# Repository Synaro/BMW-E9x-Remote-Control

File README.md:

# BMW E9x Remote Control

Contrôleur embarqué expérimental pour orchestrer des fonctions distantes sur BMW
Série E9x à partir d'un cœur logiciel déterministe, testable et indépendant du
matériel.

> [!WARNING]
> Ce dépôt n'est pas un produit prêt à installer dans un véhicule. Le firmware
> fourni reste interdit de connexion au véhicule : l'acquisition TWAI passive
> est désactivée par défaut et réservée à un bus de banc qualifié. Aucun GPIO
> d'actionneur réel n'est configuré. Toute intégration physique exige une analyse de risques, des
> interverrouillages matériels, des essais sur banc et l'intervention d'une
> personne qualifiée. Le projet ne doit pas servir à contourner un antidémarrage,
> un système antivol ou une réglementation applicable.

## État du projet

### Implémenté et vérifié hors véhicule

- cœur déterministe : modèle d'état, politique de sécurité, machine d'état,
  décisions bornées et ports d'infrastructure ;
- configuration utilisateur versionnée, validée, protégée par CRC et persistée
  dans NVS sur ESP32-S3 ;
- configurateur et simulateur Windows, scénarios synthétiques, rejeu de traces
  et injections de défauts ;
- détection abstraite de trois impulsions de verrouillage avec gardes de
  provenance, fraîcheur et ordre, mais sans liaison BMW qualifiée ;
- couche CAN générique, file RX fixe et statistiques ; le pilote ESP-IDF/TWAI
  reste désactivé par défaut, démarre en `TWAI_MODE_LISTEN_ONLY` par défaut et
  peut sélectionner explicitement `TWAI_MODE_NORMAL` sur le profil Phase 3H,
  sans exposer encore aucune API d'émission ;
- contrats Capture V2, imports tabulaires et base de preuves Phase 3C/3D en
  lecture seule ;
- télémétrie V1 limitée aux trois fonctions réellement implémentées, toutes
  désactivées par défaut ;
- suites C++, Python, PlatformIO native/ESP32-S3 et simulateur Windows exécutées
  en intégration continue.

Ces validations sont logicielles et hors véhicule. Elles ne qualifient ni le
montage électrique K-CAN, ni une fonction de démarrage réel.

### Phase 3F/3G.1 — révisions K-CAN RX-only historiques

- design `KCAN_RX_ONLY_P3F` gelé, approvisionnement audité et PCB Phase 3G.1
  conservé comme révision historique reproductible ;
- carte d'achat actuelle : **ESP32-S3-DevKitC-1-N8R8** ; les 8 MiB de PSRAM
  supplémentaires ne sont pas utilisés par le firmware ;
- composants non commandés, montage non assemblé et non qualifié
  électriquement ;
- `R_LINK_TX` physiquement DNP : aucune pièce, aucun cavalier et aucune
  continuité TX autorisés ;
- aucune connexion à la BMW avant un PASS électrique complet et documenté ;
- aucune Phase 4 active. Cette révision ne doit plus être utilisée pour une
  nouvelle fabrication.

Les sources normatives sont volontairement séparées :

- [`BOM.csv`](hardware/kcan-rxonly/BOM.csv) décrit ce qui est utilisé ;
- [`procurement.csv`](hardware/kcan-rxonly/procurement.csv) décrit ce qui doit
  être acheté, avec les SKU, quantités économiques et snapshots datés ;
- [`netlist.csv`](hardware/kcan-rxonly/netlist.csv) décrit les connexions ;
- [`wiring.md`](hardware/kcan-rxonly/wiring.md) décrit l'assemblage et les
  contrôles. En cas de divergence, aucun résumé du README ne remplace ces
  fichiers.

### Phase 3H — matériel K-CAN entièrement bidirectionnel

La carte destinée à une future fabrication est désormais la Phase 3H :

- `ESP32-S3 GPIO5/TWAI_TX -> SN74LXC1T45-Q1 -> TJA1055 TXD` est un chemin
  cuivre continu ;
- `TJA1055 RXD -> ESP32-S3 GPIO4/TWAI_RX` reste le chemin de réception ;
- aucun jumper, pont de soudure, composant DNP ou gap cuivre ne verrouille TX ;
- le DevKit reste alimenté par USB et son 5 V n'est pas relié à `5V_TJA` ;
- le rail `5V_TJA` est fourni par le `TLS715B0EJV50XUMA1` validé en Phase 3G.1 ;
- les Gerbers, drills, BOM/CPL JLCPCB, BOM/centroid NextPCB, STEP, PDF, rendus
  et manifeste SHA-256 sont régénérés sous
  [`hardware/kcan-bidirectional-pcb/`](hardware/kcan-bidirectional-pcb/) ;
- aucune commande fabricant n'a été passée et aucune émission BMW n'est
  autorisée par cette révision.

La justification électrique, les GPIO, les marges logiques et les limites sont
documentés dans
[`docs/phase3h-bidirectional-kcan.md`](docs/phase3h-bidirectional-kcan.md).

### Non implémenté ou interdit à ce stade

L'adaptateur BMW réel de verrouillage, les actionneurs, les commandes
CAS/DDE/KL50 et le remote-start actif restent absents. Le **chemin électrique**
TX existe désormais sur la carte Phase 3H, mais aucune API ou commande
d'émission véhicule n'est implémentée.
Les observations communautaires ou diagnostiques ne deviennent jamais une
commande. Aucun essai BMW, rejeu ou contournement CAS/EWS/antidémarrage n'est
autorisé par l'état actuel du dépôt.

Le moteur de rejeu accepte des tableaux bornés et des fichiers de trace
canoniques. Aucun identifiant BMW n'est supposé : le profil de référence reste
au niveau `Discovery` et toutes ses sources de signaux restent `Candidate`.

## Architecture

```text
Commande / véhicule / timers
             |
             v
        Runtime embarqué  ------>  Ports d'infrastructure
             |                    (bus, E/S, notifications)
             v
        Controller
             |
             +------> SafetyPolicy
             |
             v
      Decision + actions bornées
```

Les dépendances vont vers les abstractions : la couche application connaît le
modèle du véhicule, mais ne connaît ni Arduino, ni ESP32, ni CAN, ni GPIO.

La machine d'état utilise les états suivants : `Idle`, `Authorizing`,
`Preparing`, `Cranking`, `Running`, `AwaitingTakeover`, `DriverControl`,
`Stopping` et `Fault`. Une donnée nécessaire absente ou périmée provoque un
refus ou un passage en défaut selon le contexte.

La description détaillée se trouve dans [docs/architecture.md](docs/architecture.md)
et les invariants dans [docs/safety.md](docs/safety.md). Le système de variantes
est décrit dans [docs/vehicle-profiles.md](docs/vehicle-profiles.md).
Le déclenchement par trois verrouillages et le cycle de reprise sont spécifiés
dans [docs/remote-session.md](docs/remote-session.md).
La frontière de confiance et les limites anti-rejeu des commandes sont décrites
dans [docs/lock-command-security.md](docs/lock-command-security.md).
Le contrat du futur décodeur CAN de verrouillage est défini dans
[docs/can-lock-command-adapter.md](docs/can-lock-command-adapter.md).
Les préférences, leurs limites et leur future persistance sont décrites dans
[docs/user-configuration.md](docs/user-configuration.md).
Le catalogue des fonctions actuellement implémentées est décrit dans
[docs/feature-framework.md](docs/feature-framework.md). Les idées non livrées
sont isolées dans [docs/backlog/features.md](docs/backlog/features.md).
Le premier moteur de télémétrie et ses alertes sont décrits dans
[docs/telemetry-alerts.md](docs/telemetry-alerts.md).
Le journal binaire redondant est spécifié dans
[docs/settings-persistence.md](docs/settings-persistence.md).
Le socle ESP-IDF, ses garde-fous et sa procédure de banc sont documentés dans
[docs/esp32s3-safe-foundation.md](docs/esp32s3-safe-foundation.md).
L'acquisition passive de Phase 3 et le format Capture V2 sont décrits dans
[docs/twai-listen-only-acquisition.md](docs/twai-listen-only-acquisition.md) et
[docs/capture-format-v2.md](docs/capture-format-v2.md).
Le choix du transceiver, le schéma de banc et la qualification électrique de
Phase 3B sont figés dans
[docs/phase3b-can-bench-hardware.md](docs/phase3b-can-bench-hardware.md).
Les contrats d'intégration des futurs relevés ISTA/TestO, la provenance et la
checklist de Phase 3C sont décrits dans
[docs/phase3c-vehicle-data-intake.md](docs/phase3c-vehicle-data-intake.md).
La qualification des premières preuves réelles et les inconnues restantes sont
décrites dans
[docs/phase3d-real-evidence-qualification.md](docs/phase3d-real-evidence-qualification.md).
La préparation K-CAN passive et le design RX-only gelé sont documentés dans
[docs/phase3e-kcan-passive-acquisition.md](docs/phase3e-kcan-passive-acquisition.md)
et
[docs/phase3f-kcan-rxonly-design-freeze.md](docs/phase3f-kcan-rxonly-design-freeze.md).
L'arrêt de conception PCB Phase 3G est motivé dans
[docs/phase3g-pcb-feasibility-audit.md](docs/phase3g-pcb-feasibility-audit.md).
La révision bidirectionnelle qui remplace ces cartes pour toute future
fabrication est décrite dans
[docs/phase3h-bidirectional-kcan.md](docs/phase3h-bidirectional-kcan.md).
Le configurateur PC est décrit dans
[docs/configurator.md](docs/configurator.md).
Le protocole entre configurateur et boîtier est spécifié dans
[docs/settings-protocol.md](docs/settings-protocol.md).
Le journal sémantique borné est décrit dans
[docs/diagnostic-journal.md](docs/diagnostic-journal.md).
La cible matérielle de banc, les achats autorisés et les limites avant connexion
au véhicule sont détaillés dans
[docs/hardware-v1-reference.md](docs/hardware-v1-reference.md).
La barrière logicielle placée devant le futur pilote de sorties est spécifiée
dans [docs/actuator-safety-supervisor.md](docs/actuator-safety-supervisor.md).
Le protocole local du bac à sable graphique est documenté dans
[docs/sandbox-protocol.md](docs/sandbox-protocol.md).

## Validation locale

Prérequis : un compilateur C++17. Sous Windows avec `g++.exe` disponible :

```powershell
./scripts/test.ps1
```

Les tests de l'importeur Python n'installent aucune dépendance externe :

```powershell
python -m unittest discover -s tools -p 'test_*.py' -v
```

Compilation du firmware natif avec PlatformIO :

```powershell
pio run -e native
```

La cible exacte du prototype ESP32-S3 peut être vérifiée avec :

```powershell
pio run -e esp32s3dev
```

Cette carte est la cible du prototype de banc, pas celle de l'installation
automobile définitive. Le firmware dessert le protocole local de configuration
sur USB. L'acquisition TWAI n'est activable que par une configuration locale
`BENCH_ONLY` et ne possède aucun chemin d'émission ; aucune sortie véhicule
n'est activée.

Avec CMake :

```sh
cmake -S . -B build
cmake --build build
ctest --test-dir build --output-on-failure
```

## Organisation

```text
include/bmw_remote/domain/          Modèle métier du véhicule
include/bmw_remote/application/     Sécurité, événements, décisions, contrôleur
include/bmw_remote/infrastructure/  Contrats des adaptateurs et runtime
include/bmw_remote/simulation/      Protocole synthétique hors véhicule
libs/can-core/                       Modèle et réception CAN génériques, sans BMW
src/                                Implémentations et firmware ESP32-S3
tests/                              Scénarios hôte
tools/                              Simulateur et importeur de traces PC
vehicle-data/                       Profils, observations, preuves et imports versionnés
scenarios/                          Traces synthétiques partageables
docs/                               Architecture, sécurité et intégration
```

## Configurateur utilisateur Windows

Le fichier personnel peut être créé ou modifié sans éditer de texte à la main :

```powershell
.\scripts\configure.ps1
```

L'assistant conserve une valeur lorsque l'utilisateur appuie simplement sur
Entrée, valide toutes les limites de sûreté puis écrit
`config/user-settings.conf`. Le contrôle du capot peut notamment être placé sur
`disabled` pour une E9x qui ne possède pas ce capteur.

La configuration produite peut être contrôlée puis exécutée immédiatement dans
le simulateur :

```powershell
.\scripts\configure.ps1 -Check
.\scripts\simulate.ps1 -ConfigPath .\config\user-settings.conf
```

L'exécutable généré se trouve dans `build/bmw_remote_configurator.exe`. Le codec
et le service communiquent avec le prototype par son port série USB. Pour lister
les ports puis lire ou écrire le boîtier :

```powershell
.\scripts\configure.ps1 -ListDevices
.\scripts\configure.ps1 -ProbeDevice COM3
.\scripts\configure.ps1 -ReadDevice COM3
.\scripts\configure.ps1 -WriteDevice COM3
```

Une écriture n'est déclarée réussie qu'après relecture et comparaison complète.
Voir [docs/configurator.md](docs/configurator.md).

Le premier essai avec une carte neuve est automatisé et utilise une
configuration de banc où le démarrage distant reste désactivé :

```powershell
.\scripts\first-usb-test.ps1 -Port COM3
```

## Simulateur applicatif

Sous Windows, le moyen le plus simple est l'interface graphique :

```powershell
.\scripts\simulator-gui.ps1
```

Le fichier `scripts/start-simulator-gui.cmd` peut aussi être ouvert par double
clic. L'interface compile le simulateur uniquement lorsque ses sources sont
plus récentes, permet de choisir un scénario, un fichier de configuration ou
une trace, puis affiche et copie le rapport. Le bouton **Ouvrir le bac à sable**
garde une session vivante : l'utilisateur peut modifier les portes, le capot,
le frein, le rapport et le régime moteur, déclencher les timers et observer en
direct l'état, les sorties simulées et les défauts. Les températures moteur et
boîte, la régénération FAP et leurs trois fonctions V1 peuvent également être
injectées ou désactivées séparément. Elle reste entièrement
locale et ne se connecte à aucun véhicule.

Sous Windows, l'exécutable interactif peut être construit avec :

```powershell
.\scripts\build-simulator.ps1
.\build\bmw_remote_simulator.exe
```

Le catalogue des fonctions actuellement implémentées est affichable
sans lancer de scénario :

```powershell
.\build\bmw_remote_simulator.exe --list-features
```

Quinze scénarios permettent de tester le parcours nominal, le capot obligatoire
ou facultatif, la reprise conducteur, la perte, le retard et la corruption des
données, un profil utilisateur, la récupération du stockage et la liaison de
configuration, la garde anti-rejeu et l'adaptateur CAN qualifié sur un vecteur
fictif, le watchdog et les retours d'actionneurs simulés, ainsi que leur
propagation complète dans le runtime. Un scénario précis
peut aussi être compilé et exécuté avec :

```powershell
.\scripts\simulate.ps1 -Scenario hood-optional
.\scripts\simulate.ps1 -Scenario takeover-timeout
.\scripts\simulate.ps1 -Scenario takeover-confirmed
.\scripts\simulate.ps1 -Scenario signal-loss
.\scripts\simulate.ps1 -Scenario signal-delay
.\scripts\simulate.ps1 -Scenario frame-corruption
.\scripts\simulate.ps1 -ConfigPath .\config\user-settings.example.conf
.\scripts\simulate.ps1 -Scenario settings-recovery
.\scripts\simulate.ps1 -Scenario settings-link
.\scripts\simulate.ps1 -Scenario lock-replay-guard
.\scripts\simulate.ps1 -Scenario qualified-lock-adapter
.\scripts\simulate.ps1 -Scenario actuator-supervisor
.\scripts\simulate.ps1 -Scenario supervised-runtime
```

Chaque parcours affiche aussi le journal chronologique des commandes,
transitions, refus et défauts. Le résultat attendu est affiché sous la forme
`scenario_result: PASS` et le code de sortie reste non nul si le comportement
diverge.

Voir [docs/simulator.md](docs/simulator.md) pour la CLI et
[docs/can-replay.md](docs/can-replay.md) pour le contrat du moteur de rejeu.

Le simulateur accepte aussi une trace canonique externe :

```powershell
./scripts/simulate.ps1 ./scenarios/synthetic_idle.cantrace.csv
```

Pour convertir une capture reconnue par `python-can`, voir
[docs/trace-import.md](docs/trace-import.md). Les captures privées restent hors
du dépôt via `captures/private/`.

Une comparaison synthétique capot fermé / ouvert peut être lancée avec :

```powershell
./scripts/analyze-trace-change.ps1 `
  ./scenarios/synthetic_idle.cantrace.csv `
  ./scenarios/synthetic_hood_open.cantrace.csv
```

Le protocole destiné aux premières observations réelles est décrit dans
[docs/read-only-discovery.md](docs/read-only-discovery.md).

Une session privée d'inventaire K+DCAN peut être préparée sans enregistrer le
VIN :

```powershell
.\scripts\new-diagnostic-session.ps1 -SessionName e90-reference-01
```

Voir [docs/diagnostic-inventory.md](docs/diagnostic-inventory.md) avant d'ouvrir
une fonction dans ISTA, INPA ou Tool32.

Pour VS Code, PlatformIO génère localement `.vscode/c_cpp_properties.json` avec
les paramètres de l'environnement actif ; ce fichier reste hors Git car il
contient des chemins propres à la machine. `compile_flags.txt` configure le mode
de repli de `clangd`. Si d'anciens diagnostics restent affichés après une mise à
jour, exécuter `PlatformIO: Rebuild IntelliSense Index`, puis
`C/C++: Reset IntelliSense Database` et recharger la fenêtre.

## Capture CAN passive

Un outil PC peut produire directement une trace canonique depuis une interface
`python-can` dont le mode silencieux a été intégré explicitement :

```powershell
.\scripts\capture-can-trace.ps1 `
  -Interface pcan `
  -Channel PCAN_USBBUS1 `
  -Bitrate 500000 `
  -Duration 10 `
  -OutputPath .\captures\private\session-01\baseline.cantrace.csv
```

Le débit ci-dessus est uniquement un exemple et doit être confirmé avant la
connexion. L'outil ne contient aucun appel d'émission et refuse les pilotes non
qualifiés. Le câble K+DCAN reste réservé au diagnostic : il n'est pas supposé
fournir une capture CAN brute. Voir
[docs/capture-qualification.md](docs/capture-qualification.md).

## Principes de contribution

Toute évolution doit conserver la séparation entre métier et matériel, échouer
de manière sûre, rester déterministe et ajouter des tests aux nouvelles
transitions. Voir [CONTRIBUTING.md](CONTRIBUTING.md).

## Origine et inspiration

Le concept général est inspiré du dépôt
[AlbertoMarziali/bmw_remote_start](https://github.com/AlbertoMarziali/bmw_remote_start).
Ce projet est une implémentation indépendante : aucun code du dépôt de référence
n'a été copié. L'objectif est une architecture plus modulaire, explicite et
adaptée à une validation progressive.

## Licence

Distribué sous licence MIT. Voir [LICENSE](LICENSE).

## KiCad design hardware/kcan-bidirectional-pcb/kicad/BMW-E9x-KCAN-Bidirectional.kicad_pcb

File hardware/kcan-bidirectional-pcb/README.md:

# Phase 3H — carte K-CAN bidirectionnelle

Ce dossier définit la révision matérielle destinée à remplacer la carte
RX-only Phase 3G/3G.1 pour une future fabrication. Les dossiers et tags des
anciennes phases restent historiques et ne sont pas modifiés.

La carte Phase 3H fournit les deux chemins électriques complets :

```text
GPIO5 / TWAI_TX -> R5 -> U2 A -> U2 B -> U1 TXD -> K-CAN
K-CAN -> U1 RXD -> R7 -> GPIO4 / TWAI_RX
```

U2 est un `SN74LXC1T45QDCKRQ1` alimenté en 3,3 V côté A et 5 V côté B.
Il remplace le buffer mono-alimentation Phase 3G. Il ne constitue pas un
verrou : `DIR` est fixé à A vers B et le chemin TX est toujours câblé.

Il n'existe aucun jumper TX, pont de soudure, composant DNP, `R_LINK_TX`, zone
keepout ou coupure cuivre permettant/désactivant la transmission. Le mode
listen-only reste disponible uniquement comme configuration logicielle TWAI.

## Contenu

- `kicad/` : schéma et PCB KiCad 10 Phase 3H ;
- `BOM_PHASE3H.csv` : BOM normative par carte ;
- `netlist_PHASE3H.csv` : connexions normatives et chemins fonctionnels ;
- `pin-review.csv` : revue des broches critiques ;
- `procurement_PHASE3H.csv` : références de sourcing, sans ordre d'achat ;
- `manufacturing/` : artefacts régénérés depuis cette révision uniquement.

La régénération s'effectue avec :

```powershell
python tools/generate_phase3h_kicad.py schematic
& 'C:\Users\synar\AppData\Local\Programs\KiCad\10.0\bin\python.exe' tools/generate_phase3h_kicad.py pcb
./tools/generate_phase3h_manufacturing.ps1
./tools/generate_phase3h_nextpcb.ps1
```

Ces commandes ne contactent aucun fabricant et ne passent aucune commande.

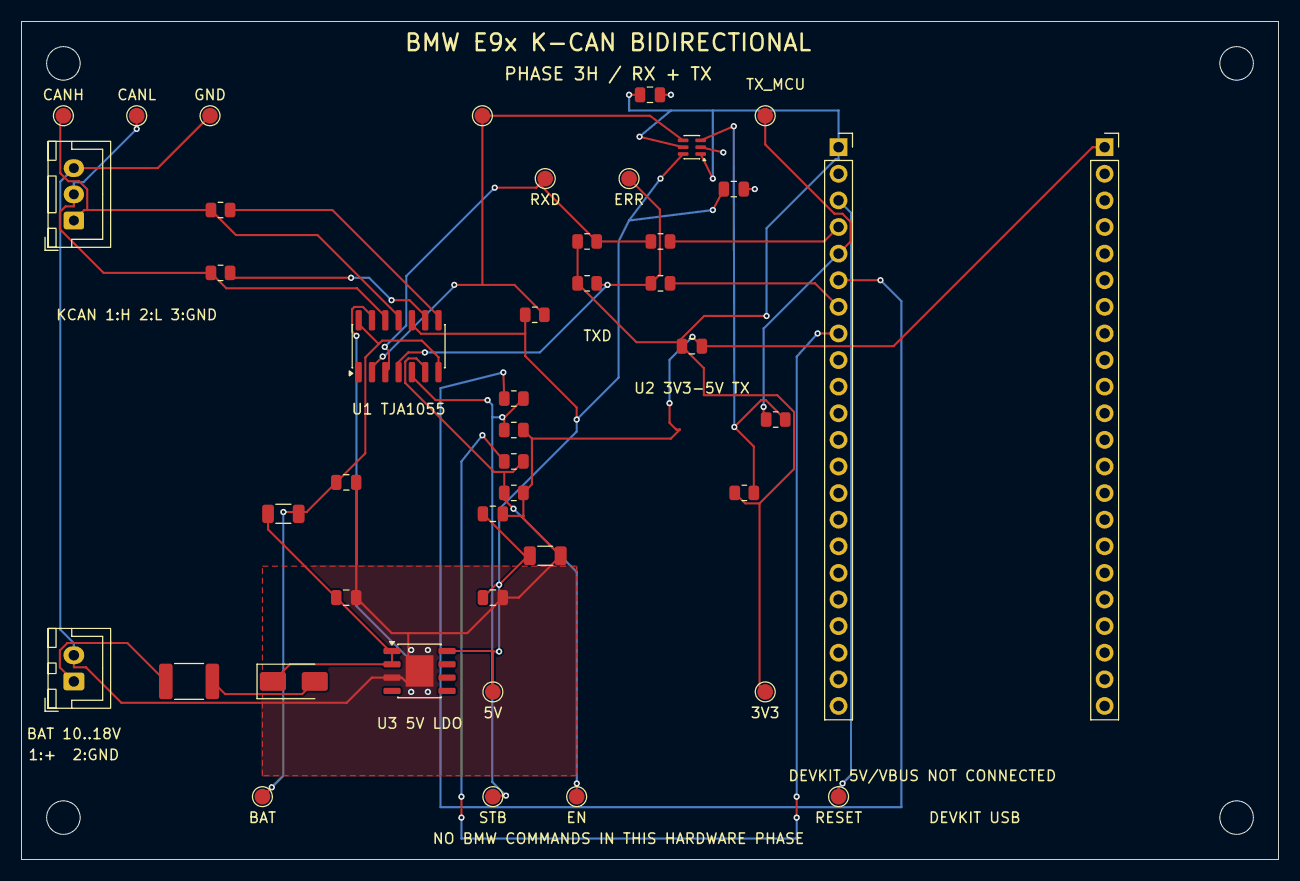
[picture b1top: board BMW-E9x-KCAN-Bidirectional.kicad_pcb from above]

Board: 2 copper layers, 120.0 x 80.0 mm, 48 parts (0 on the bottom side), 23 nets.

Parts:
C1: C_REG_IN 100n 50V; C_0805_2012Metric
C2: C_REG_OUT 2.2u 25V; C_0805_2012Metric
C3: C_VCC 100n; C_0805_2012Metric
C4: C_VCC 22u 10V; C_1206_3216Metric
C5: C_BAT 10n 50V; C_0805_2012Metric
C6: C_U2 100n; C_0805_2012Metric
C7: 100n / C_U2_5V; C_0805_2012Metric
C8: 100n / C_U2_3V3; C_0805_2012Metric
D1: D_BAT SS16; D_SMA
F1: F_BAT MINISMDC010F-2; Fuse_1812_4532Metric_Pad1.30x3.40mm_Reviewed
H1: ESP32-S3 DEVKIT J1; PinSocket_1x22_P2.54mm_Vertical
H2: ESP32-S3 DEVKIT J3; PinSocket_1x22_P2.54mm_Vertical
J1: J_BAT 10..18V BENCH; JST_XH_B2B-XH-A_1x02_P2.50mm_Vertical
J2: J_KCAN H L GND; JST_XH_B3B-XH-A_1x03_P2.50mm_Vertical
MH1, MH2, MH3, MH4: M3; MountingHole_3.2mm_M3
R1: R_BAT 1k; R_1206_3216Metric
R2: R_TXD 10k; R_0805_2012Metric
R4: R_A 100k; R_0805_2012Metric
R5: R_TX_SER 1k; R_0805_2012Metric
R6: R_RX_PULL 3.3k; R_0805_2012Metric
R7: R_RX_SER 1k; R_0805_2012Metric
R8: R_ERR_PULL 3.3k; R_0805_2012Metric
R9: R_ERR_SER 1k; R_0805_2012Metric
R10: R_STB_SER 1k; R_0805_2012Metric
R11: R_STB_PD 10k; R_0805_2012Metric
R12: R_EN_SER 1k; R_0805_2012Metric
R13: R_EN_PD 10k; R_0805_2012Metric
R14: R_RTH 5.62k; R_0805_2012Metric
R15: R_RTL 5.62k; R_0805_2012Metric
TP1: BAT; TestPoint_Pad_D1.5mm
TP2: 5V; TestPoint_Pad_D1.5mm
TP3: 3V3; TestPoint_Pad_D1.5mm
TP5: TXD; TestPoint_Pad_D1.5mm
TP7: TWAI_TX; TestPoint_Pad_D1.5mm
TP8: RESET; TestPoint_Pad_D1.5mm
TP9: STB; TestPoint_Pad_D1.5mm
TP10: EN; TestPoint_Pad_D1.5mm
TP11: RXD; TestPoint_Pad_D1.5mm
TP12: ERR; TestPoint_Pad_D1.5mm
TP13: CANH; TestPoint_Pad_D1.5mm
TP14: CANL; TestPoint_Pad_D1.5mm
TP15: GND; TestPoint_Pad_D1.5mm
U1: TJA1055T/3/2Z; SO-14_3.9x8.65mm_P1.27mm
U2: SN74LXC1T45QDCKRQ1; SOT-363_SC-70-6
U3: TLS715B0EJV50XUMA1; Infineon_PG-DSO-8-52_3.9x4.9mm_EP2.65x3mm_NoViaInPad

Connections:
3V3: C6.1, C8.1, H1.1, R4.1, R6.1, R8.1, TP3.1, U2.1, U2.5
5V_TJA: C2.1, C3.1, C4.1, C7.1, R2.1, TP2.1, U1.10, U2.6, U3.8
BAT_FUSED: D1.2, F1.2
BAT_INPUT: F1.1, J1.1
BAT_LOCAL: C5.1, R1.2, TP1.1, U1.7, U1.14
BAT_PROTECTED: C1.1, D1.1, R1.1, U3.1, U3.2
GND: C1.2, C2.2, C3.2, C4.2, C5.2, C6.2, C7.2, C8.2, H2.1, J1.2, J2.3, R11.2, R13.2, TP15.1, U1.13, U2.2, U3.3, U3.9
KCAN_EN: R12.2, R13.1, TP10.1, U1.6
KCAN_EN_MCU: H1.8, R12.1
KCAN_ERR_MCU: H1.7, R9.2
KCAN_ERR_OD: R8.2, R9.1, TP12.1, U1.4
KCAN_H: J2.1, R14.1, TP13.1, U1.11
KCAN_L: J2.2, R15.1, TP14.1, U1.12
KCAN_RXD_OD: R6.2, R7.1, TP11.1, U1.3
KCAN_RX_MCU: H1.4, R7.2
KCAN_STB: R10.2, R11.1, TP9.1, U1.5
KCAN_STB_MCU: H1.6, R10.1
KCAN_TXD: R2.2, TP5.1, U1.2, U2.4
KCAN_TX_A: R4.2, R5.2, U2.3
KCAN_TX_MCU: H1.5, R5.1, TP7.1
RESET: H1.3, TP8.1
RTH: R14.2, U1.8
RTL: R15.2, U1.9

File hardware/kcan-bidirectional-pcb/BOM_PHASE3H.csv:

reference,quantity,manufacturer,mpn,value,package,assembly,role
U1,1,NXP,TJA1055T/3/2Z,TJA1055T/3,SO-14_3.9x8.7mm,MOUNT,ISO11898-3 full bidirectional K-CAN transceiver
U2,1,Texas Instruments,SN74LXC1T45QDCKRQ1,SN74LXC1T45-Q1,SC70-6 DCK,MOUNT,Automotive dual-supply 3V3-to-5V TX translator
U3,1,Infineon,TLS715B0EJV50XUMA1,5V 150mA,PG-DSO-8-52 EP,MOUNT,Dedicated 5V_TJA regulator
DEV1,1,Espressif Systems,ESP32-S3-DEVKITC-1-N8R8,DevKitC-1,Removable module,USER_INSTALL,USB-powered TWAI controller
H1 H2,2,Samtec,SSQ-122-03-G-S,1x22 female,2.54mm THT,MOUNT,DevKit sockets
F1,1,Littelfuse,MINISMDC010F-2,0.10A hold,1812,MOUNT,F_BAT input current protection
D1,1,Vishay,SS16-E3/61T,SS16 / D_BAT,SMA,MOUNT,Input reverse-polarity protection
R1,1,Yageo,RC1206FR-071KL,1k 1%,1206,MOUNT,R_BAT TJA BAT series
R2 R11 R13,3,Yageo,RC0805FR-0710KL,10k 1%,0805,MOUNT,TXD recessive bias and STB EN reset pulldowns
R4,1,Yageo,RC0805FR-07100KL,100k 1%,0805,MOUNT,U2 A input recessive bias
R5 R7 R9 R10 R12,5,Yageo,RC0805FR-071KL,1k 1%,0805,MOUNT,TX RX ERR STB EN series resistors
R6 R8,2,Yageo,RC0805FR-073K3L,3.3k 1%,0805,MOUNT,RXD ERR open-drain pull-ups to 3V3
R14 R15,2,Yageo,RT0805BRD075K62L,5.62k 0.1%,0805,MOUNT,RTH RTL weak matched LSFT termination
C1 C3 C6 C7 C8,5,Wurth Elektronik,885012207098,100nF 50V X7R,0805,MOUNT,Input VCC and dual-rail logic decoupling
C5,1,Wurth Elektronik,885012207092,10nF 50V X7R,0805,MOUNT,C_BAT TJA BAT local
C2,1,TDK,CGA4J3X7R1E225K125AB,2.2uF 25V X7R,0805,MOUNT,C_REG_OUT U3 stability
C4,1,Murata,GCM31CR71A226ME02L,22uF 10V X7R,1206,MOUNT,C_VCC TJA reservoir
J1,1,JST,B2B-XH-A(LF)(SN),2-pin XH,2.50mm THT,MOUNT,J_BAT bench power
J2,1,JST,B3B-XH-A(LF)(SN),3-pin XH,2.50mm THT,MOUNT,J_KCAN bench bus
TP1 TP2 TP3 TP5 TP7 TP8 TP9 TP10 TP11 TP12 TP13 TP14 TP15,13,PCB FABRICATED,TEST_PAD_1P5,Test pad,1.5mm exposed copper,FABRICATED,BAT 5V 3V3 TXD TX_MCU RESET STB EN RXD ERR CANH CANL GND
MH1 MH2 MH3 MH4,4,PCB FABRICATED,M3_NPTH,3.2mm mounting hole,NPTH,FABRICATED,Mechanical mounting only

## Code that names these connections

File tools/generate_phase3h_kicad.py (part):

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
    sch.add_text("POWER: 10..18V -> F_BAT -> D_BAT -> TLS715B0EJV50 -> 5V_TJA", (80, 25), size=1.5)
    sch.add_text("ESP32 USB ONLY — DEVKIT 5V PIN NC — COMMON GND ONLY", (70, 32), size=1.5)
    sch.add_text("FULL TX: GPIO5 -> R5 -> U2 A/B -> KCAN_TXD -> U1.TXD", (205, 32), size=1.5)
    sch.add_text("U2 VCCA=3V3, VCCB=5V_TJA, DIR=3V3; NO TX JUMPER OR GAP", (205, 39), size=1.3)
    sch.save_as(OUT / f"{NAME}.kicad_sch")

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    for name in [
        "GND","3V3","BAT_INPUT","BAT_FUSED","BAT_PROTECTED","BAT_LOCAL","5V_TJA",
        "TXD_SAFE","TX_GPIO","TX_GATE_IN","TX_GATE_OUT","OE_SAFE","RXD_OD","RXD_GPIO",
        "ERR_OD","ERR_GPIO","RX_MODE_FEED","STB_SAFE","EN_SAFE","RTH","RTL","KCAN_H",
        "KCAN_L","RESET",
    ]:
        net = pcbnew.NETINFO_ITEM(board, name)
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    board_text = remove_expressions(board_text, "gr_text", lambda _: True)

    for old_name, new_name in {
        "TX_GPIO": "KCAN_TX_MCU",
        "TX_GATE_IN": "KCAN_TX_A",
        "TXD_SAFE": "KCAN_TXD",
        "RXD_OD": "KCAN_RXD_OD",
        "RXD_GPIO": "KCAN_RX_MCU",
        "ERR_OD": "KCAN_ERR_OD",
        "ERR_GPIO": "KCAN_ERR_MCU",
        "STB_SAFE": "KCAN_STB",
        "EN_SAFE": "KCAN_EN",
    }.items():
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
